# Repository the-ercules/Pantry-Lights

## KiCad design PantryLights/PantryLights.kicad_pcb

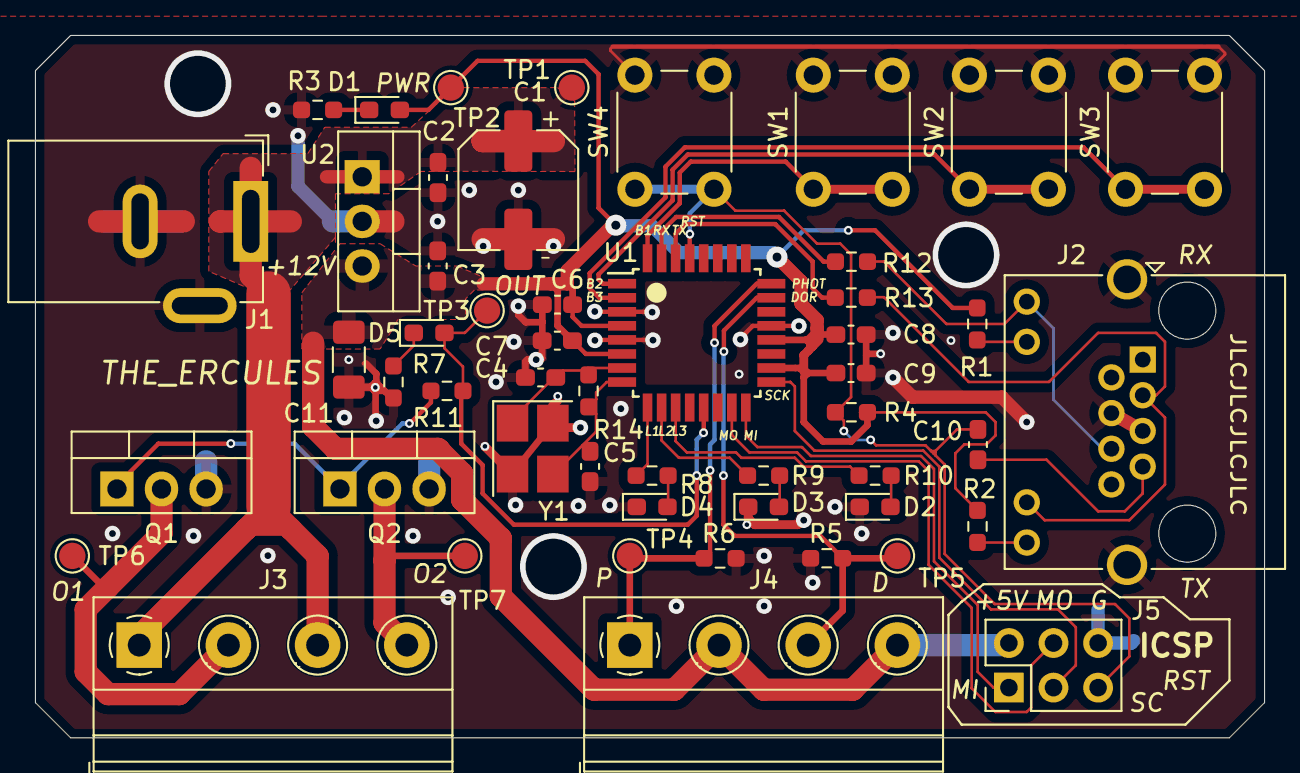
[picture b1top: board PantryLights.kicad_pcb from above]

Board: 2 copper layers, 70.0 x 40.0 mm, 51 parts (0 on the bottom side), 33 nets.

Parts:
C1: 22u; CP_Elec_6.3x5.9
C2, C3, C6, C7, C8, C9, C10: 100n; C_0603_1608Metric_Pad1.08x0.95mm_HandSolder
C4, C5: 18p; C_0603_1608Metric_Pad1.08x0.95mm_HandSolder
C11: 4.7u; C_1206_3216Metric_Pad1.33x1.80mm_HandSolder
D1, D5: RED; LED_0603_1608Metric_Pad1.05x0.95mm_HandSolder
D2, D3, D4: GREEN; LED_0603_1608Metric_Pad1.05x0.95mm_HandSolder
J1: Barrel_Jack_Switch; BarrelJack_GCT_DCJ200-10-A_Horizontal
J2: 8P8C_LED_Shielded; RJ45_Amphenol_RJHSE538X
J3, J4: Conn_01x04; TerminalBlock_Right-Angle_Modular-1,5-4-5.08_1x04_P5.08mm_H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
J5: Conn_02x03_Counter_Clockwise; PinHeader_2x03_P2.54mm_Vertical
Q1, Q2: IRF540N; TO-220-3_Vertical
R1, R2: 150R; R_0603_1608Metric_Pad0.98x0.95mm_HandSolder
R3, R7: 750R; R_0603_1608Metric_Pad0.98x0.95mm_HandSolder
R4, R5: 10K; R_0603_1608Metric_Pad0.98x0.95mm_HandSolder
R6: 5K; R_0603_1608Metric_Pad0.98x0.95mm_HandSolder
R8, R9, R10: 600R; R_0603_1608Metric_Pad0.98x0.95mm_HandSolder
R11: 220R; R_0603_1608Metric_Pad0.98x0.95mm_HandSolder
R12, R13: 1K; R_0603_1608Metric_Pad0.98x0.95mm_HandSolder
R14: 1M; R_0603_1608Metric_Pad0.98x0.95mm_HandSolder
SW1, SW2, SW3, SW4: SW_MEC_5E; SW_PUSH_6mm_H5mm_4pin
TP1, TP2, TP3, TP4, TP5, TP6, TP7: TestPoint; TestPoint_Pad_D1.5mm
U1: ATmega328P-A; TQFP-32_7x7mm_P0.8mm
U2: LM7805_TO220; TO-220-3_Vertical
Y1: 16MHz; Crystal_SMD_3225-4Pin_3.2x2.5mm_HandSoldering

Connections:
+5V: C3.1, C6.1, C7.1, C8.2, C9.2, C11.1, D1.2 (A), J4.2, J4.4, J5.2, R1.1, R2.1, R4.2, TP2.1, U1.4 (VCC), U1.6 (VCC), U1.18 (AVCC), U1.20 (AREF), U2.3 (VO)
+12V: C1.1, C2.1, J1.1, J3.1, J3.3, TP1.1, U2.1 (VI)
/BTN_1: SW1.1, SW1.2, U1.32 (PD2)
/BTN_2: SW2.1, SW2.2, U1.1 (PD3)
/BTN_3: SW3.1, SW3.2, U1.2 (PD4)
/DOOR_SW_IN: J4.3, R5.2, TP5.1, U1.23 (PC0)
/LED_1: R8.1, U1.9 (PD5)
/LED_2: R9.1, U1.10 (PD6)
/LED_3: R10.1, U1.11 (PD7)
/LIGHTS_CL: Q1.1 (G), Q2.1 (G), R11.2
/LIGHT_SIGNAL: D5.2 (A), R11.1, TP3.1, U1.13 (PB1)
/OSC_A: C4.2, R14.2, U1.7 (XTAL1/PB6), Y1.1
/OSC_B: C5.2, R14.1, U1.8 (XTAL2/PB7), Y1.3
/PHOTORESISTOR_IN: J4.1, R6.1, TP4.1, U1.24 (PC1)
GND: C1.2, C2.2, C3.2, C4.1, C5.1, C6.2, C7.2, C8.1, C9.1, C11.2, D2.1 (K), D3.1 (K), D4.1 (K), J1.2, J1.3, J2.4, J2.5, J2.SH, J5.6, Q1.3 (S), Q2.3 (S), R3.2, R5.1, R6.2, R7.2, SW1.3 (K), SW1.4 (A), SW2.3 (K), SW2.4 (A), SW3.3 (K), SW3.4 (A), SW4.1, SW4.2, U1.3 (GND), U1.5 (GND), U1.21 (GND), U2.2 (GND), Y1.2, Y1.4
MISO: J5.1, U1.16 (PB4)
MOSI: J5.4, U1.15 (PB3)
unnamed: C10.1, J2.7
unnamed: D1.1 (K), R3.1
unnamed: D5.1 (K), R7.1
unnamed: J2.6, J2.9, R12.2
unnamed: J2.10, R1.2
unnamed: J2.3, J2.11, R13.2
unnamed: J2.12, R2.2
unnamed: J3.2, Q1.2 (D), TP6.1
unnamed: J3.4, Q2.2 (D), TP7.1
unnamed: D4.2 (A), R8.2
unnamed: D3.2 (A), R9.2
unnamed: D2.2 (A), R10.2
RESET: C10.2, J5.5, R4.1, SW4.3 (K), SW4.4 (A), U1.29 (~RESET/PC6)
RX: R12.1, U1.31 (PD1)
SCK: J5.3, U1.17 (PB5)
TX: R13.1, U1.30 (PD0)

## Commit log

2022-01-11 Initial Working Code
    This version works on the bench with the minimum feature-set, but is not quite ready for beta.
    TODO:
    - EEPROM integration
    - menu timeout (no save)
    - menu interface changes (maybe dedicated LED?)
    - Remove serial debugging output
2022-01-12 Beta-Ready
    REV 0.2.2 : Beta
    Software is now where I want it to be. Fully user configurable, with EEPROM to save important values. Also added panic mode to load factory defaults into ram (Can lock in by skipping through all sett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
    Decided not to add additional output LED since the main lights are a good enough interface
    Added menu timeout, we'll see if 5 mins is long enough.
    Framework for debugging is there, but not quite good. Maybe add a debugging option in the settings menu in the future?
2022-01-15 Updating for actual prototype
    Changed buttons, added more debug data, and added local copies of dependencies.
2022-01-15 Adding break between debug entries
2022-01-20 Schematic and prelim PCB layout
2022-01-27 Added Gerbers per REV_1
2022-02-18 Second PCB Revision
2022-05-29 Board Order
